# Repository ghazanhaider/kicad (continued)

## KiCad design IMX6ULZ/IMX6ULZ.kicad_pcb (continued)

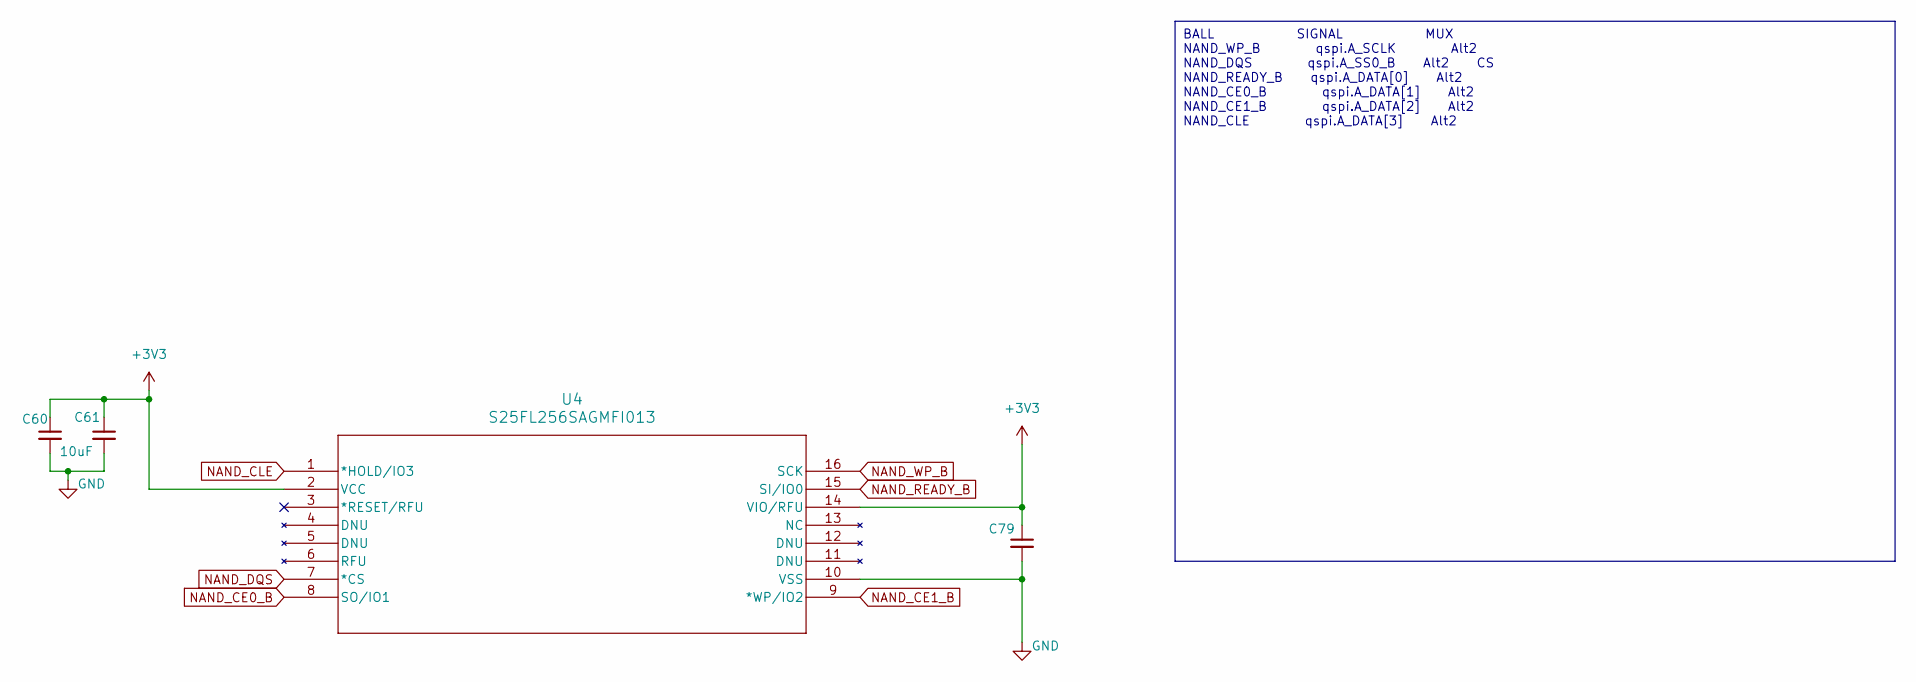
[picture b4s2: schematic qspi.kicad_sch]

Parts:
C60, C79: 0.22uF; C_0402_1005Metric
C61: 10uF; C_0402_1005Metric
U4: S25FL256SAGMFI013; SO3016_SPA

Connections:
3V3: C60.1, C61.1, C79.1, U4.2 (VCC), U4.14 (VIO/RFU); also elsewhere on the board
GND: C60.2, C61.2, C79.2, U4.10 (VSS); also elsewhere on the board
NAND_CE0_B: U4.8 (SO/IO1); also elsewhere on the board
NAND_CE1_B: U4.9 (*WP/IO2); also elsewhere on the board
NAND_CLE: U4.1 (*HOLD/IO3); also elsewhere on the board
NAND_DQS: U4.7 (*CS); also elsewhere on the board
NAND_READY_B: U4.15 (SI/IO0); also elsewhere on the board
NAND_WP_B: U4.16 (SCK); also elsewhere on the board

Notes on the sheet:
BALL SIGNAL MUX NAND_WP_B qspi.A_SCLK Alt2 NAND_DQS qspi.A_SS0_B Alt2 CS NAND_READY_B qspi.A_DATA[0] Alt2 NAND_CE0_B qspi.A_DATA[1] Alt2 NAND_CE1_B qspi.A_DATA[2] Alt2 NAND_CLE qspi.A_DATA[3] Alt2

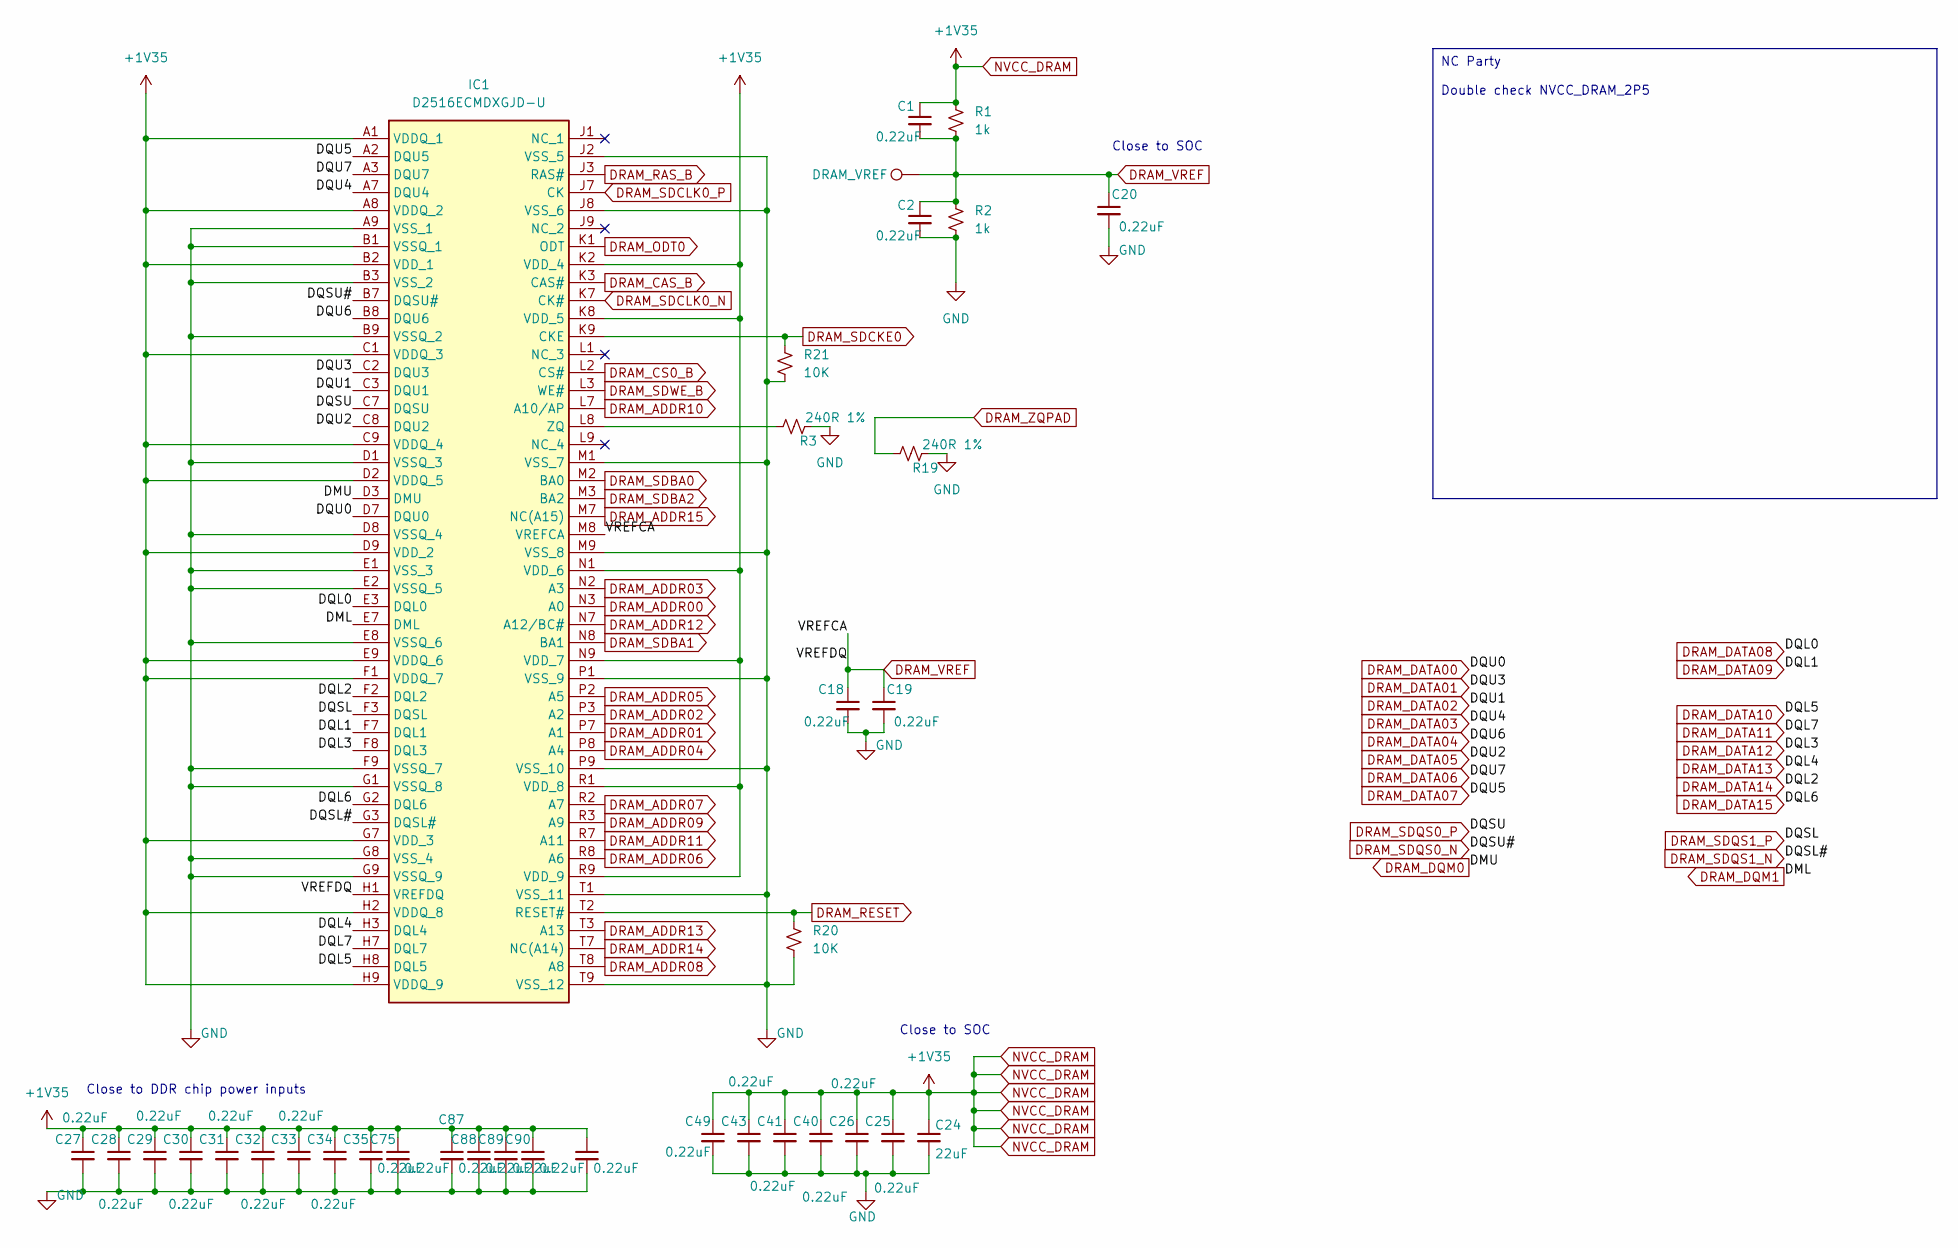
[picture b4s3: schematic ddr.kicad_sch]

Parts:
C1, C2, C18, C19: 0.22uF; C_0402_1005Metric
C20, C25, C26, C27, C28, C29, C30, C31, C32, C33, C34, C35, C40, C41, C43, C49, C75, C87, C88, C89, C90, C92: 0.22uF; C_0201_0603Metric
C24: 22uF; C_0402_1005Metric
IC1: D2516ECMDXGJD-U; Micron_FBGA-96_7.5x13.5mm_Layout9x16_P0.8mm; Mouser Part Number D1216ECMDXGJD-U
R1, R2: 1k; R_0402_1005Metric
R3, R19: 240R 1%; R_0402_1005Metric
R20, R21: 10K; R_0402_1005Metric
TP5: DRAM_VREF; TestPoint_Pad_D1.0mm

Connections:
1V35: C1.1, C24.1, C25.1, C26.1, C27.1, C28.1, C29.1, C30.1, C31.1, C32.1, C33.1, C34.1, C35.1, C40.1, C41.1, C43.1, C49.1, C75.1, C87.1, C88.1, C89.1, C90.1, C92.1, IC1.A1 (VDDQ_1), IC1.A8 (VDDQ_2), IC1.B2 (VDD_1), IC1.C1 (VDDQ_3), IC1.C9 (VDDQ_4), IC1.D2 (VDDQ_5), IC1.D9 (VDD_2), IC1.E9 (VDDQ_6), IC1.F1 (VDDQ_7), IC1.G7 (VDD_3), IC1.H2 (VDDQ_8), IC1.H9 (VDDQ_9), IC1.K2 (VDD_4), IC1.K8 (VDD_5), IC1.N1 (VDD_6), IC1.N9 (VDD_7), IC1.R1 (VDD_8), IC1.R9 (VDD_9), R1.1; also elsewhere on the board
DRAM_ADDR00: IC1.N3 (A0); also elsewhere on the board
DRAM_ADDR01: IC1.P7 (A1); also elsewhere on the board
DRAM_ADDR02: IC1.P3 (A2); also elsewhere on the board
DRAM_ADDR03: IC1.N2 (A3); also elsewhere on the board
DRAM_ADDR04: IC1.P8 (A4); also elsewhere on the board
DRAM_ADDR05: IC1.P2 (A5); also elsewhere on the board
DRAM_ADDR06: IC1.R8 (A6); also elsewhere on the board
DRAM_ADDR07: IC1.R2 (A7); also elsewhere on the board
DRAM_ADDR08: IC1.T8 (A8); also elsewhere on the board
DRAM_ADDR09: IC1.R3 (A9); also elsewhere on the board
DRAM_ADDR10: IC1.L7 (A10/AP); also elsewhere on the board
DRAM_ADDR11: IC1.R7 (A11); also elsewhere on the board
DRAM_ADDR12: IC1.N7 (A12/BC#); also elsewhere on the board
DRAM_ADDR13: IC1.T3 (A13); also elsewhere on the board
DRAM_ADDR14: IC1.T7 (NC(A14)); also elsewhere on the board
DRAM_ADDR15: IC1.M7 (NC(A15)); also elsewhere on the board
DRAM_CAS_B: IC1.K3 (CAS#); also elsewhere on the board
DRAM_CS0_B: IC1.L2 (CS#); also elsewhere on the board
DRAM_DATA00: IC1.D7 (DQU0); also elsewhere on the board
DRAM_DATA01: IC1.C2 (DQU3); also elsewhere on the board
DRAM_DATA02: IC1.C3 (DQU1); also elsewhere on the board
DRAM_DATA03: IC1.A7 (DQU4); also elsewhere on the board
DRAM_DATA04: IC1.B8 (DQU6); also elsewhere on the board
DRAM_DATA05: IC1.C8 (DQU2); also elsewhere on the board
DRAM_DATA06: IC1.A3 (DQU7); also elsewhere on the board
DRAM_DATA07: IC1.A2 (DQU5); also elsewhere on the board
DRAM_DATA08: IC1.E3 (DQL0); also elsewhere on the board
DRAM_DATA09: IC1.F7 (DQL1); also elsewhere on the board
DRAM_DATA10: IC1.H8 (DQL5); also elsewhere on the board
DRAM_DATA11: IC1.H7 (DQL7); also elsewhere on the board
DRAM_DATA12: IC1.F8 (DQL3); also elsewhere on the board
DRAM_DATA13: IC1.H3 (DQL4); also elsewhere on the board
DRAM_DATA14: IC1.F2 (DQL2); also elsewhere on the board
DRAM_DATA15: IC1.G2 (DQL6); also elsewhere on the board
DRAM_DQM0: IC1.D3 (DMU); also elsewhere on the board
DRAM_DQM1: IC1.E7 (DML); also elsewhere on the board
DRAM_ODT0: IC1.K1 (ODT); also elsewhere on the board
DRAM_RAS_B: IC1.J3 (RAS#); also elsewhere on the board
DRAM_RESET: IC1.T2 (RESET#), R20.1; also elsewhere on the board
DRAM_SDBA0: IC1.M2 (BA0); also elsewhere on the board
DRAM_SDBA1: IC1.N8 (BA1); also elsewhere on the board
DRAM_SDBA2: IC1.M3 (BA2); also elsewhere on the board
DRAM_SDCKE0: IC1.K9 (CKE), R21.1; also elsewhere on the board
DRAM_SDCLK0_N: IC1.K7 (CK#); also elsewhere on the board
DRAM_SDCLK0_P: IC1.J7 (CK); also elsewhere on the board
DRAM_SDQS0_N: IC1.B7 (DQSU#); also elsewhere on the board
DRAM_SDQS0_P: IC1.C7 (DQSU); also elsewhere on the board
DRAM_SDQS1_N: IC1.G3 (DQSL#); also elsewhere on the board
DRAM_SDQS1_P: IC1.F3 (DQSL); also elsewhere on the board
DRAM_SDWE_B: IC1.L3 (WE#); also elsewhere on the board
DRAM_VREF: C1.2, C2.1, C18.1, C19.1, C20.1, IC1.H1 (VREFDQ), IC1.M8 (VREFCA), R1.2, R2.1, TP5.1; also elsewhere on the board
DRAM_ZQPAD: R19.1; also elsewhere on the board
GND: C2.2, C18.2, C19.2, C20.2, C24.2, C25.2, C26.2, C27.2, C28.2, C29.2, C30.2, C31.2, C32.2, C33.2, C34.2, C35.2, C40.2, C41.2, C43.2, C49.2, C75.2, C87.2, C88.2, C89.2, C90.2, C92.2, IC1.A9 (VSS_1), IC1.B1 (VSSQ_1), IC1.B3 (VSS_2), IC1.B9 (VSSQ_2), IC1.D1 (VSSQ_3), IC1.D8 (VSSQ_4), IC1.E1 (VSS_3), IC1.E2 (VSSQ_5), IC1.E8 (VSSQ_6), IC1.F9 (VSSQ_7), IC1.G1 (VSSQ_8), IC1.G8 (VSS_4), IC1.G9 (VSSQ_9), IC1.J2 (VSS_5), IC1.J8 (VSS_6), IC1.M1 (VSS_7), IC1.M9 (VSS_8), IC1.P1 (VSS_9), IC1.P9 (VSS_10), IC1.T1 (VSS_11), IC1.T9 (VSS_12), R2.2, R3.2, R19.2, R20.2, R21.2; also elsewhere on the board
unnamed: IC1.L8 (ZQ), R3.1

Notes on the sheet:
NC Party Double check NVCC_DRAM_2P5
Close to SOC
Close to DDR chip power inputs

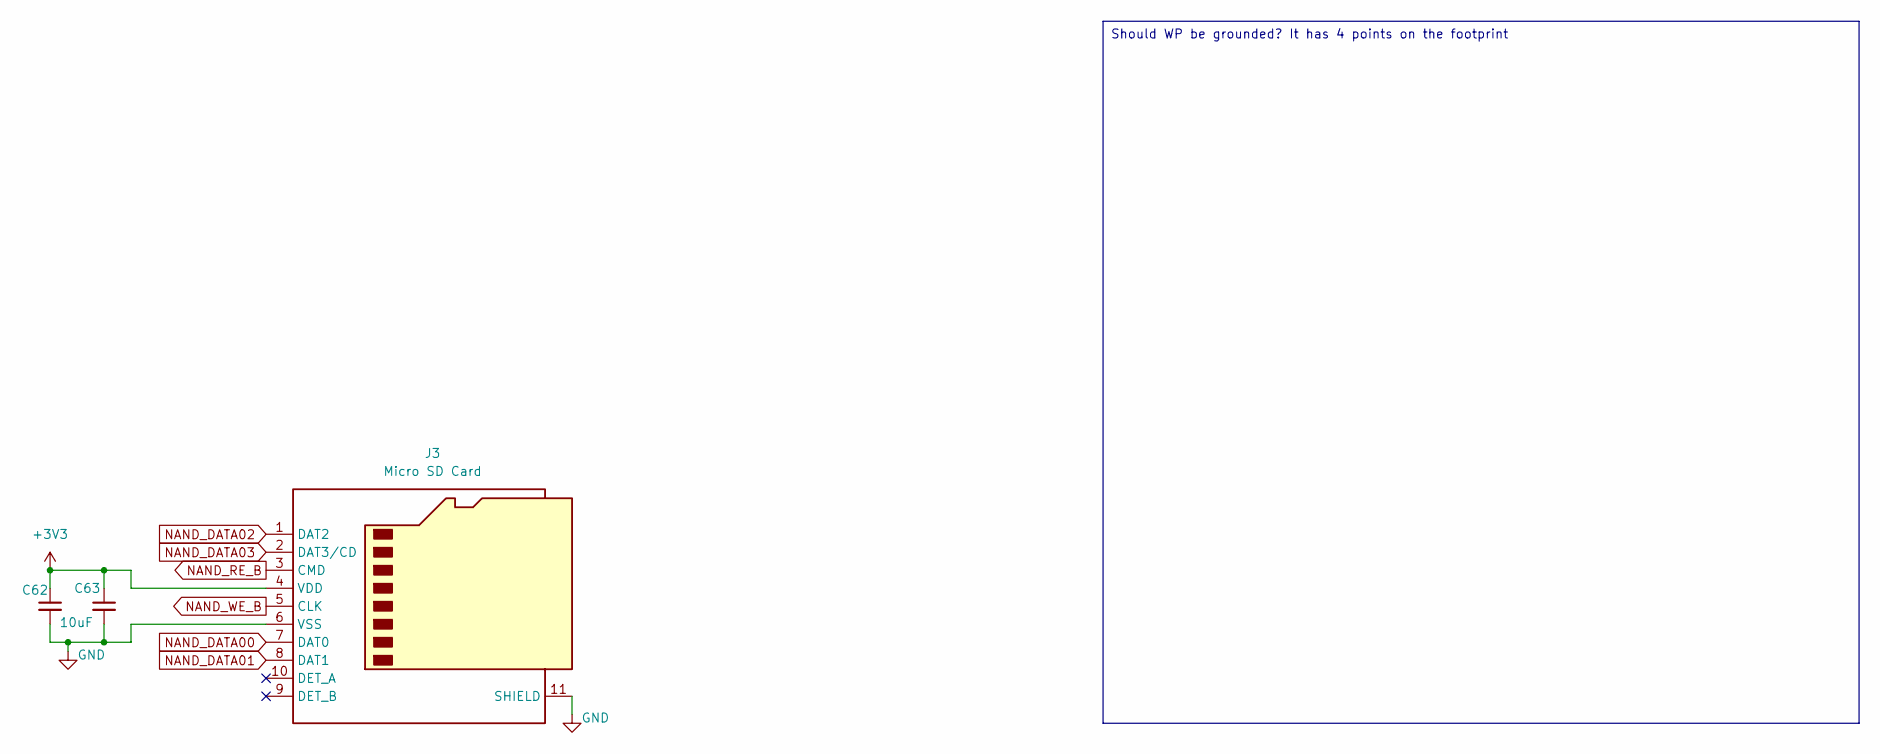
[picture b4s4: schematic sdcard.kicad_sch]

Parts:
C62: 0.22uF; C_0402_1005Metric
C63: 10uF; C_0402_1005Metric
J3: Micro SD Card; microSD_HC_Hirose_DM3D-SF

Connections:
3V3: C62.1, C63.1, J3.4 (VDD); also elsewhere on the board
GND: C62.2, C63.2, J3.6 (VSS), J3.11 (SHIELD); also elsewhere on the board
NAND_DATA00: J3.7 (DAT0); also elsewhere on the board
NAND_DATA01: J3.8 (DAT1); also elsewhere on the board
NAND_DATA02: J3.1 (DAT2); also elsewhere on the board
NAND_DATA03: J3.2 (DAT3/CD); also elsewhere on the board
NAND_RE_B: J3.3 (CMD); also elsewhere on the board
NAND_WE_B: J3.5 (CLK); also elsewhere on the board

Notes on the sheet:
Should WP be grounded? It has 4 points on the footprint

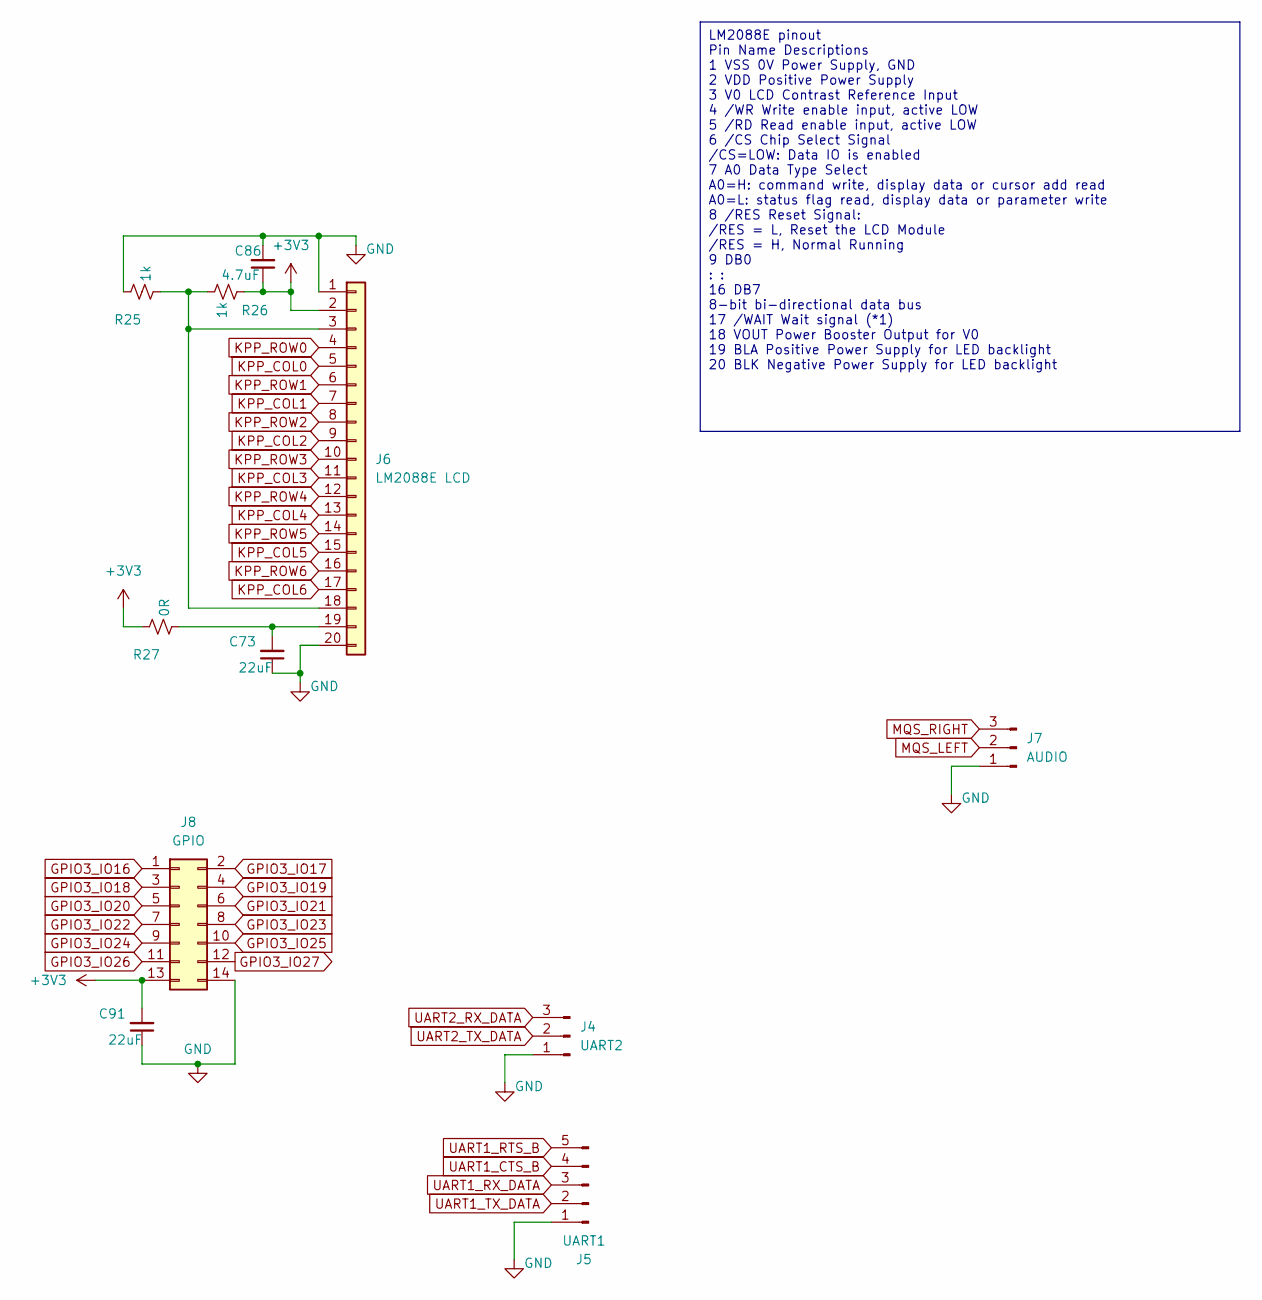
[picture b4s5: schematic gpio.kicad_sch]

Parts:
C73, C91: 22uF; C_0805_2012Metric
C86: 4.7uF; C_0805_2012Metric
J4: UART2; PinHeader_1x03_P2.54mm_Vertical
J5: UART1; PinHeader_1x05_P2.54mm_Vertical
J6: LM2088E LCD; PinHeader_1x20_P2.54mm_Vertical
J7: AUDIO; PinHeader_1x03_P2.54mm_Vertical
J8: GPIO; PinHeader_2x07_P2.54mm_Vertical
R25, R26: 1k; R_0402_1005Metric
R27: 0R; R_0805_2012Metric

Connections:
3V3: C86.1, C91.2, J6.2, J8.13, R26.1, R27.1; also elsewhere on the board
GND: C73.1, C86.2, C91.1, J4.1, J5.1, J6.1, J6.20, J7.1, J8.14, R25.1; also elsewhere on the board
GPIO3_IO16: J8.1; also elsewhere on the board
GPIO3_IO17: J8.2; also elsewhere on the board
GPIO3_IO18: J8.3; also elsewhere on the board
GPIO3_IO19: J8.4; also elsewhere on the board
GPIO3_IO20: J8.5; also elsewhere on the board
GPIO3_IO21: J8.6; also elsewhere on the board
GPIO3_IO22: J8.7; also elsewhere on the board
GPIO3_IO23: J8.8; also elsewhere on the board
GPIO3_IO24: J8.9; also elsewhere on the board
GPIO3_IO25: J8.10; also elsewhere on the board
GPIO3_IO26: J8.11; also elsewhere on the board
GPIO3_IO27: J8.12; also elsewhere on the board
KPP_COL0: J6.5; also elsewhere on the board
KPP_COL1: J6.7; also elsewhere on the board
KPP_COL2: J6.9; also elsewhere on the board
KPP_COL3: J6.11; also elsewhere on the board
KPP_COL4: J6.13; also elsewhere on the board
KPP_COL5: J6.15; also elsewhere on the board
KPP_COL6: J6.17; also elsewhere on the board
KPP_ROW0: J6.4; also elsewhere on the board
KPP_ROW1: J6.6; also elsewhere on the board
KPP_ROW2: J6.8; also elsewhere on the board
KPP_ROW3: J6.10; also elsewhere on the board
KPP_ROW4: J6.12; also elsewhere on the board
KPP_ROW5: J6.14; also elsewhere on the board
KPP_ROW6: J6.16; also elsewhere on the board
MQS_LEFT: J7.2; also elsewhere on the board
MQS_RIGHT: J7.3; also elsewhere on the board
unnamed: J6.3, J6.18, R25.2, R26.2
unnamed: C73.2, J6.19, R27.2
UART1_CTS_B: J5.4; also elsewhere on the board
UART1_RTS_B: J5.5; also elsewhere on the board
UART1_RX_DATA: J5.3; also elsewhere on the board
UART1_TX_DATA: J5.2; also elsewhere on the board
UART2_RX_DATA: J4.3; also elsewhere on the board
UART2_TX_DATA: J4.2; also elsewhere on the board

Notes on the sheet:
LM2088E pinout Pin Name Descriptions 1 VSS 0V Power Supply, GND 2 VDD Positive Power Supply 3 V0 LCD Contrast Reference Input 4 /WR Write enable input, active LOW 5 /RD Read enable input, active LOW 6 /CS Chip Select Signal /CS=LOW: Data IO is enabled 7 A0 Data Type Select A0=H: command write, disp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

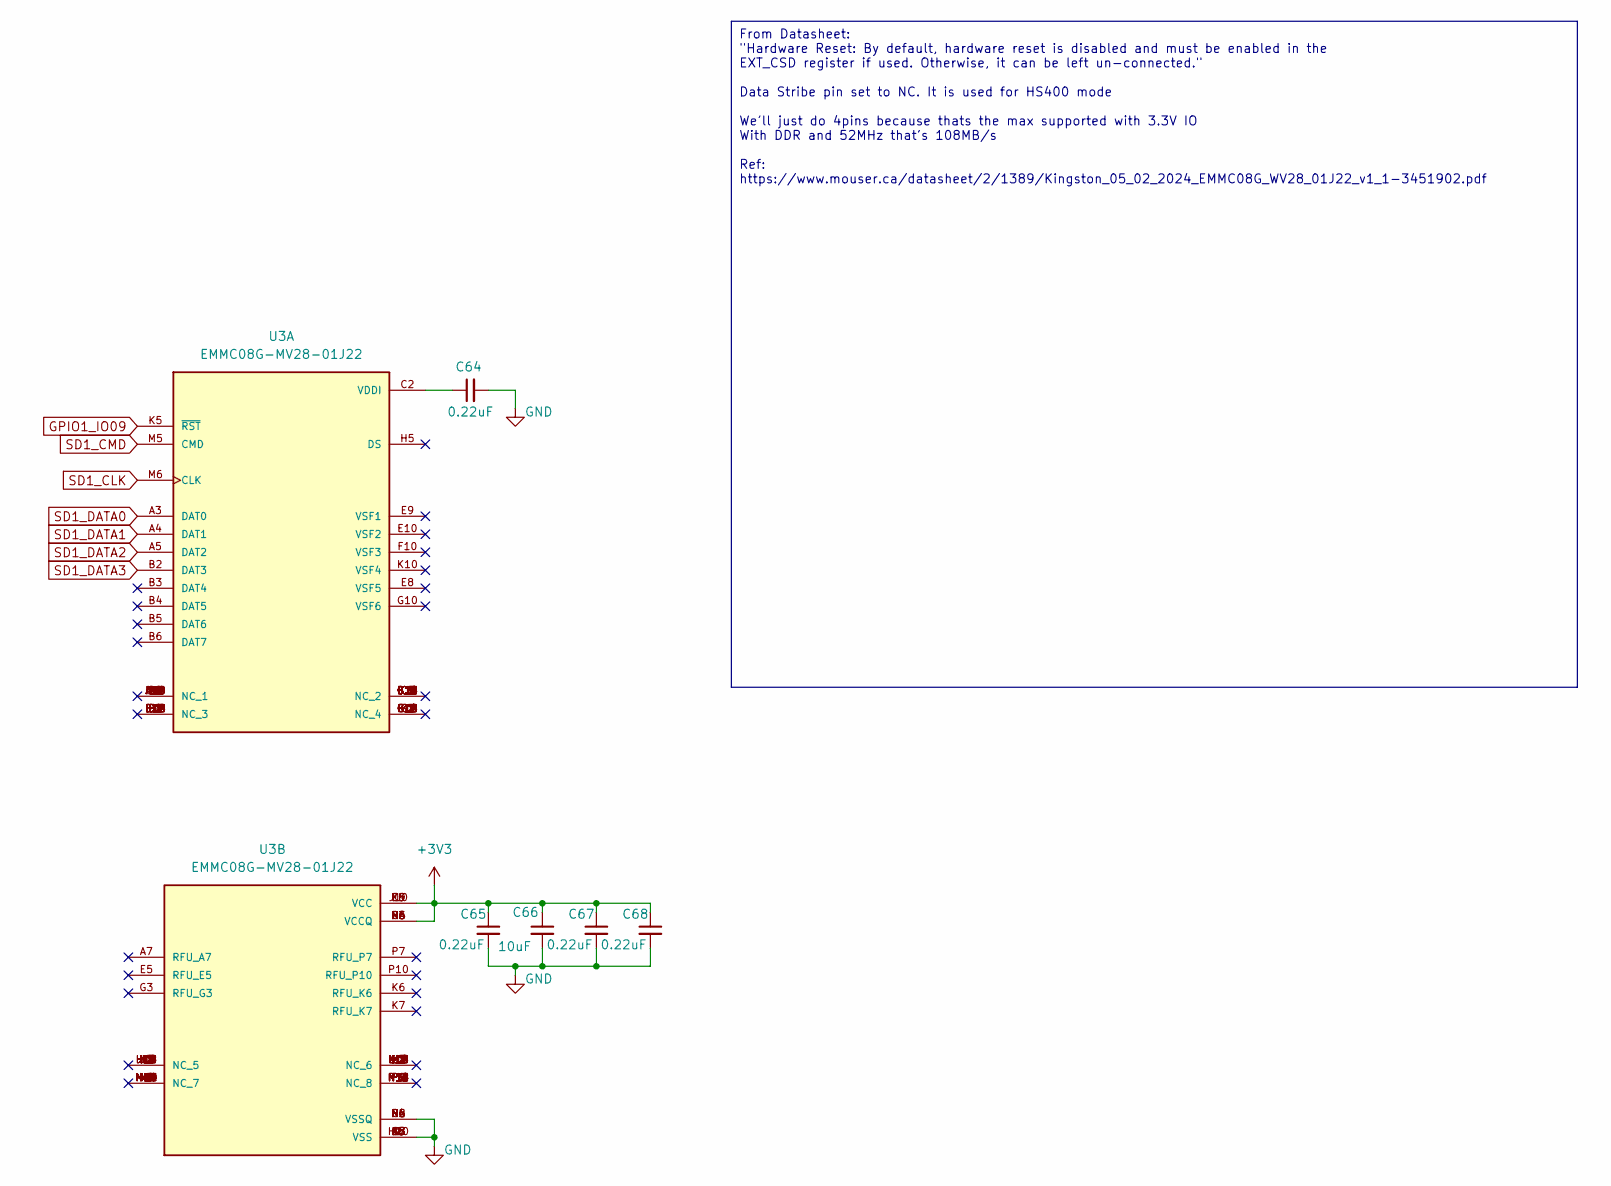
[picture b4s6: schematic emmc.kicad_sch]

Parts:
C64, C65, C67, C68: 0.22uF; C_0402_1005Metric
C66: 10uF; C_0402_1005Metric
U3: EMMC08G-MV28-01J22; BGA153N50P14X14_1300X1150X100N; PARTREV N/A

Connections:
3V3: C65.1, C66.1, C67.1, C68.1, U3.C6 (VCCQ), U3.E6 (VCC), U3.F5 (VCC), U3.J10 (VCC), U3.K9 (VCC), U3.M4 (VCCQ), U3.N4 (VCCQ), U3.P3 (VCCQ), U3.P5 (VCCQ); also elsewhere on the board
GND: C64.2, C65.2, C66.2, C67.2, C68.2, U3.A6 (VSS), U3.C4 (VSSQ), U3.E7 (VSS), U3.G5 (VSS), U3.H10 (VSS), U3.J5 (VSS), U3.K8 (VSS), U3.N2 (VSSQ), U3.N5 (VSSQ), U3.P4 (VSSQ), U3.P6 (VSSQ); also elsewhere on the board
GPIO1_IO09: U3.K5 (~RST); also elsewhere on the board
unnamed: C64.1, U3.C2 (VDDI)
SD1_CLK: U3.M6 (CLK); also elsewhere on the board
SD1_CMD: U3.M5 (CMD); also elsewhere on the board
SD1_DATA0: U3.A3 (DAT0); also elsewhere on the board
SD1_DATA1: U3.A4 (DAT1); also elsewhere on the board
SD1_DATA2: U3.A5 (DAT2); also elsewhere on the board
SD1_DATA3: U3.B2 (DAT3); also elsewhere on the board

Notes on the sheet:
From Datasheet: "Hardware Reset: By default, hardware reset is disabled and must be enabled in the EXT_CSD register if used. Otherwise, it can be left un-connected." Data Stribe pin set to NC. It is used for HS400 mode We'll just do 4pins because thats the max supported with 3.3V IO With DDR and 52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

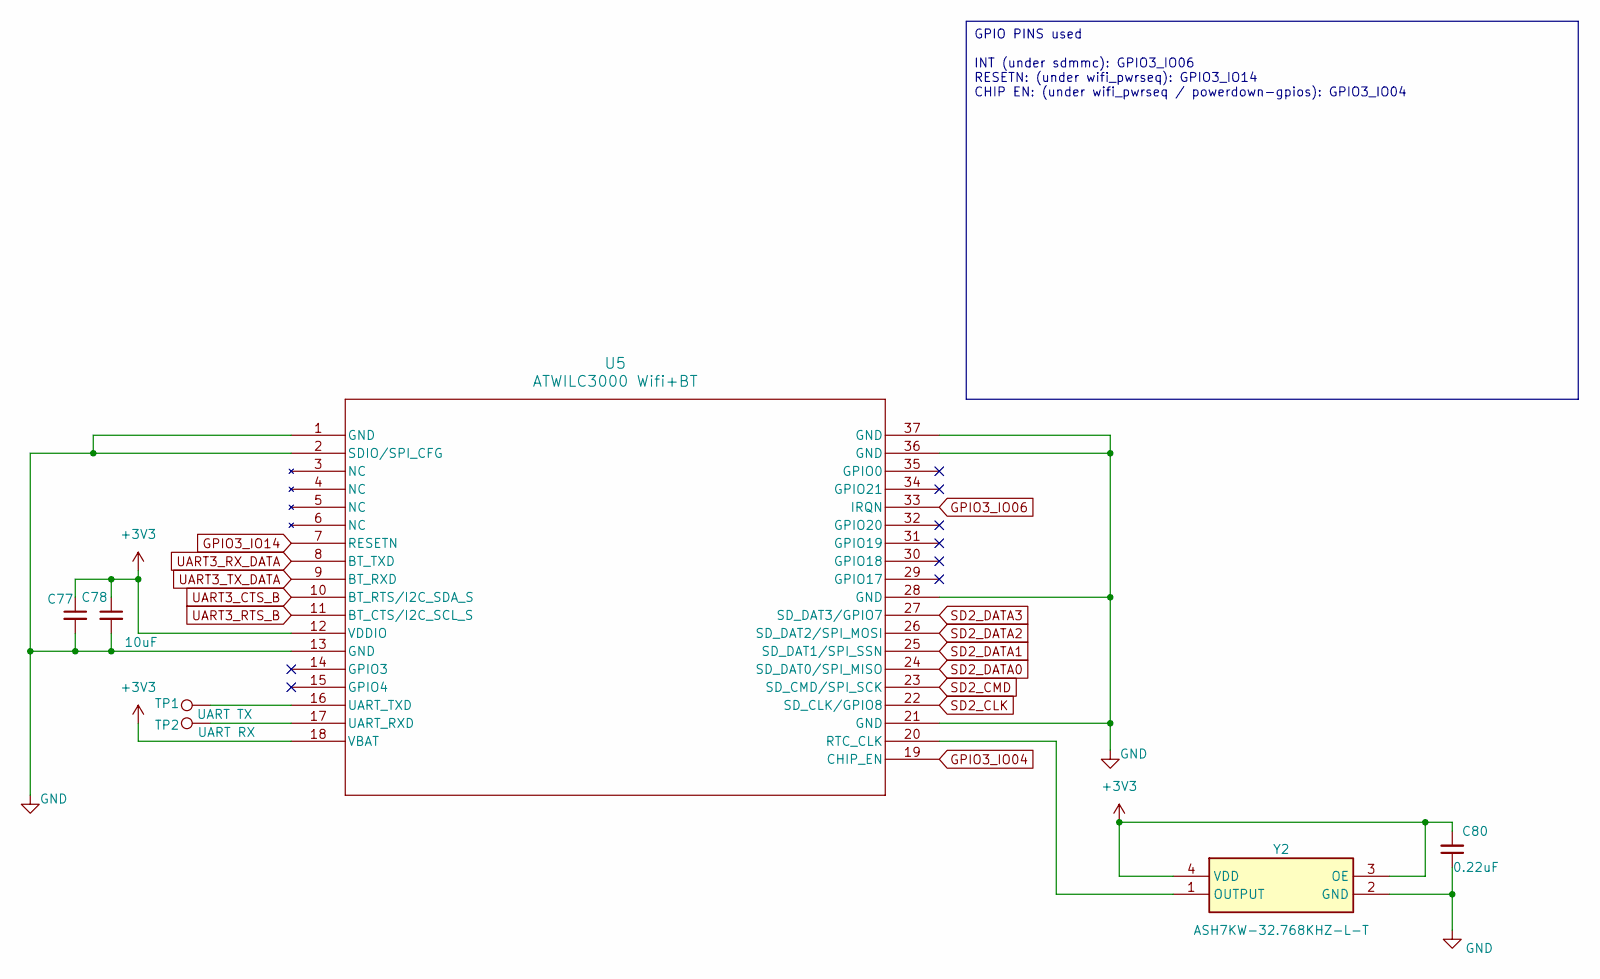
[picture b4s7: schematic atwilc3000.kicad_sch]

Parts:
C77, C80: 0.22uF; C_0402_1005Metric
C78: 10uF; C_0402_1005Metric
TP1: UART TX; TestPoint_Pad_D1.0mm
TP2: UART RX; TestPoint_Pad_D1.0mm
U5: ATWILC3000 Wifi+BT; ATWILC3000-MR110CA_MCH
Y2: ASH7KW-32.768KHZ-L-T; ASH7KW32768kHzLT; Mouser Part Number 815-ASH7KW-32.7-L-T

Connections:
3V3: C77.1, C78.1, C80.2, U5.12 (VDDIO), U5.18 (VBAT), Y2.3 (OE), Y2.4 (VDD); also elsewhere on the board
GND: C77.2, C78.2, C80.1, U5.1 (GND), U5.2 (SDIO/SPI_CFG), U5.13 (GND), U5.21 (GND), U5.28 (GND), U5.36 (GND), U5.37 (GND), Y2.2 (GND); also elsewhere on the board
GPIO3_IO04: U5.19 (CHIP_EN); also elsewhere on the board
GPIO3_IO06: U5.33 (IRQN); also elsewhere on the board
GPIO3_IO14: U5.7 (RESETN); also elsewhere on the board
unnamed: U5.20 (RTC_CLK), Y2.1 (OUTPUT)
unnamed: TP2.1, U5.17 (UART_RXD)
unnamed: TP1.1, U5.16 (UART_TXD)
SD2_CLK: U5.22 (SD_CLK/GPIO8); also elsewhere on the board
SD2_CMD: U5.23 (SD_CMD/SPI_SCK); also elsewhere on the board
SD2_DATA0: U5.24 (SD_DAT0/SPI_MISO); also elsewhere on the board
SD2_DATA1: U5.25 (SD_DAT1/SPI_SSN); also elsewhere on the board
SD2_DATA2: U5.26 (SD_DAT2/SPI_MOSI); also elsewhere on the board
SD2_DATA3: U5.27 (SD_DAT3/GPIO7); also elsewhere on the board
UART3_CTS_B: U5.10 (BT_RTS/I2C_SDA_S); also elsewhere on the board
UART3_RTS_B: U5.11 (BT_CTS/I2C_SCL_S); also elsewhere on the board
UART3_RX_DATA: U5.8 (BT_TXD); also elsewhere on the board
UART3_TX_DATA: U5.9 (BT_RXD); also elsewhere on the board

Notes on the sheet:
GPIO PINS used INT (under sdmmc): GPIO3_IO06 RESETN: (under wifi_pwrseq): GPIO3_IO14 CHIP EN: (under wifi_pwrseq / powerdown-gpios): GPIO3_IO04

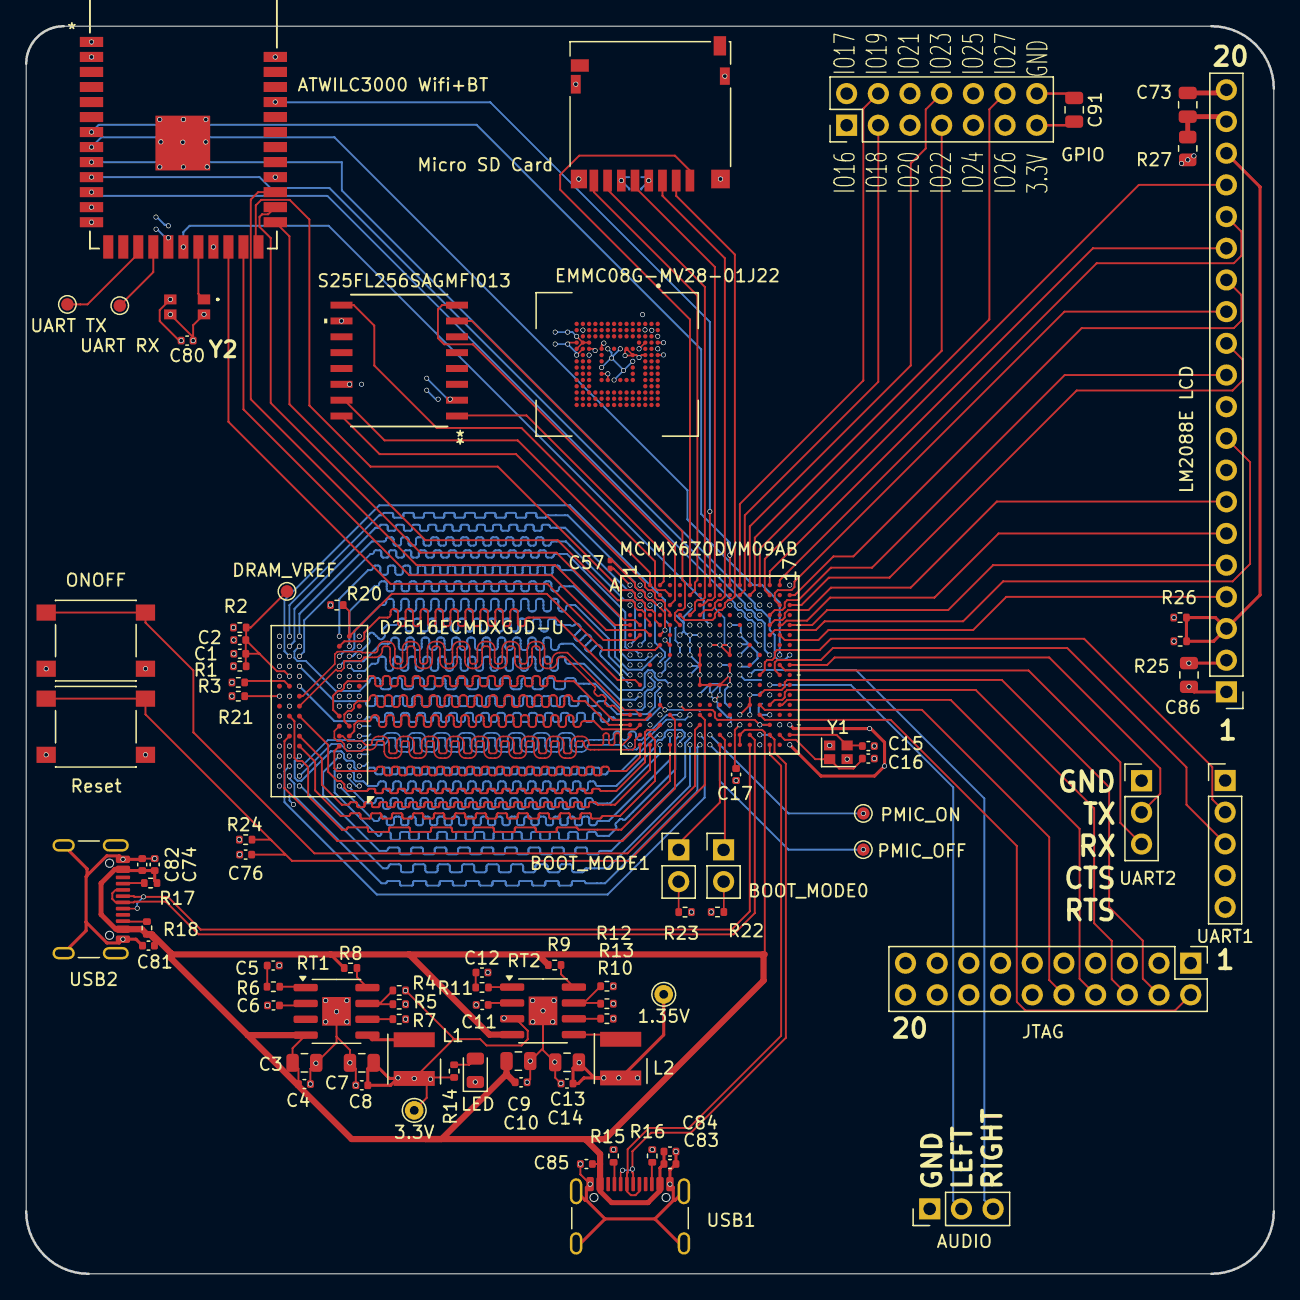
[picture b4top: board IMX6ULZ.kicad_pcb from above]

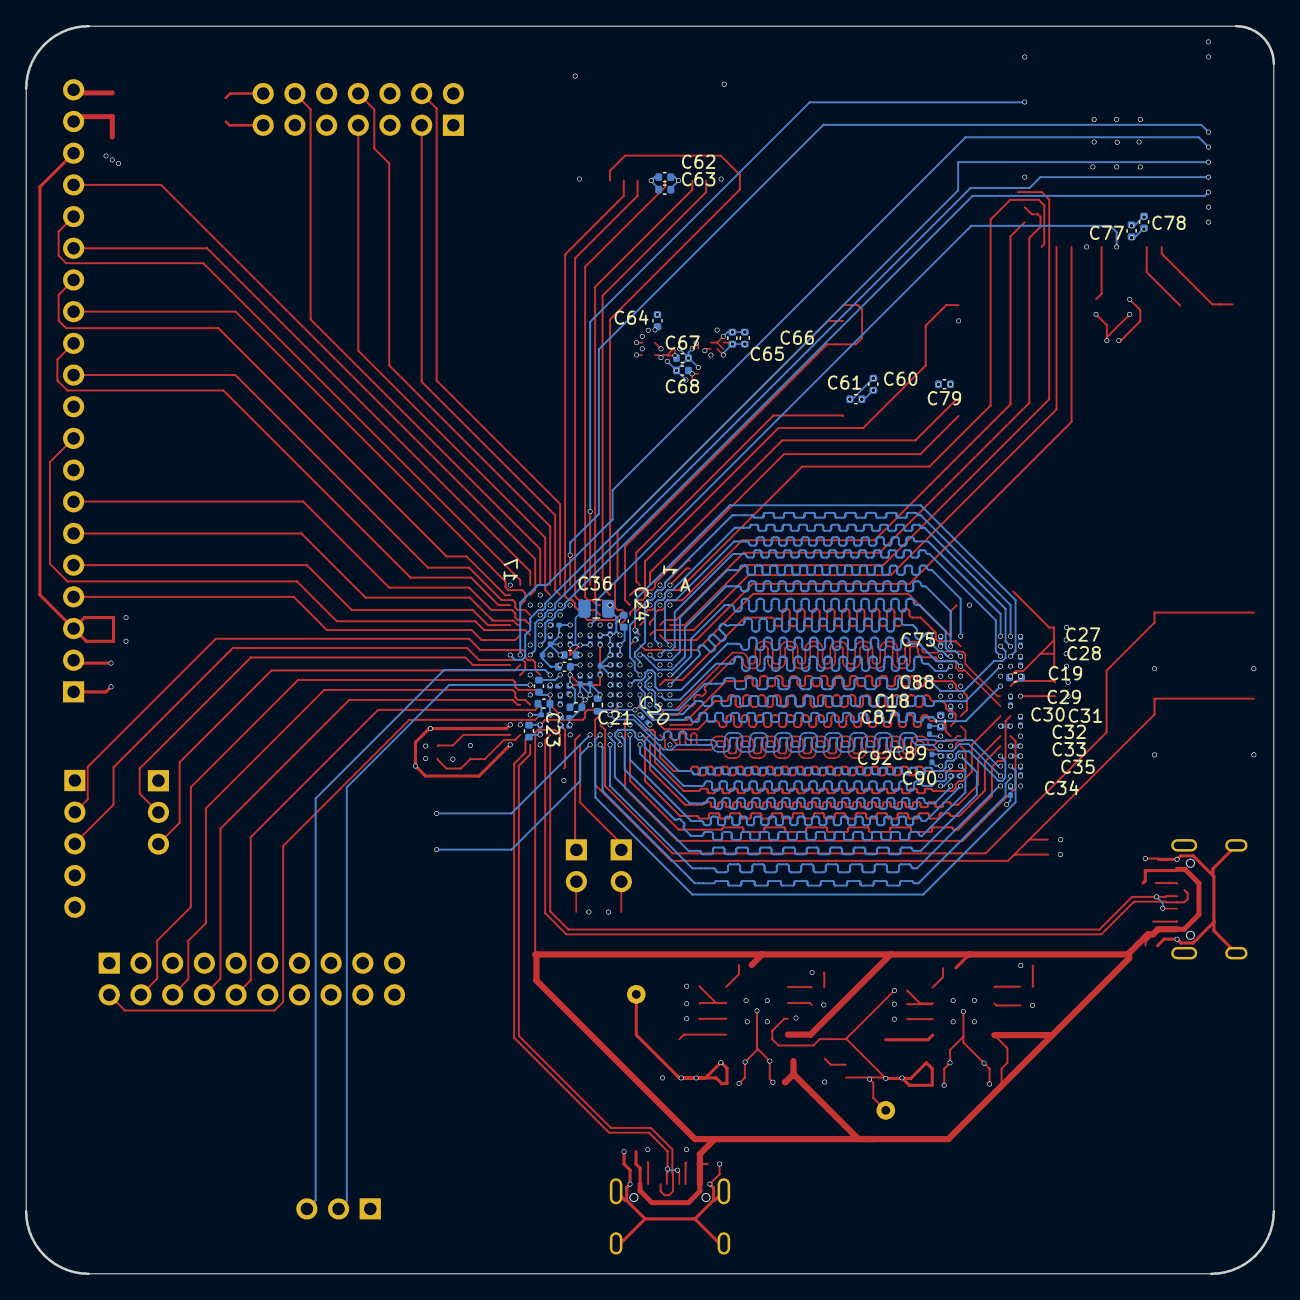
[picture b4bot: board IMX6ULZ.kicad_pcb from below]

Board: 6 copper layers, 100.0 x 100.0 mm, 151 parts (64 on the bottom side), 173 nets.

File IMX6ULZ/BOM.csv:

"Reference","Value","Footprint","Qty","DNP"
"SW1","ONOFF","Button_Switch_SMD:SW_SPST_PTS645","1",""
"SW2","Reset","Button_Switch_SMD:SW_SPST_PTS645","1",""
"C22,C25,C26,C27,C28,C29,C30,C31,C32,C33,C34,C35,C37,C38,C39,C40,C41,C42,C43,C45,C46,C47,C49,C50,C51,C52,C53,C54,C55,C57,C58,C69,C71,C72,C75,C87,C88,C89,C90,C92","0.22uF","Capacitor_SMD:C_0201_0603Metric","40",""
"C20","0.22uF","Capacitor_SMD:C_0201_0603Metric_Pad0.64x0.40mm_HandSolder","1",""
"C1,C2,C6,C11,C18,C19,C60,C62,C65,C76,C77,C79,C80,C82,C85","0.22uF","Capacitor_SMD:C_0402_1005Metric","15",""
"C4,C8,C10,C14,C21,C64,C67,C68","0.1uF","Capacitor_SMD:C_0402_1005Metric","8",""
"C5,C12","560pF","Capacitor_SMD:C_0402_1005Metric","2",""
"C15,C16","10pF","Capacitor_SMD:C_0402_1005Metric","2",""
"C17,C23,C48,C61,C63,C66,C78","10uF","Capacitor_SMD:C_0402_1005Metric","7",""
"C24,C44,C59,C81,C84","22uF","Capacitor_SMD:C_0402_1005Metric","5",""
"C56,C70,C74,C83","4.7uF","Capacitor_SMD:C_0402_1005Metric","4",""
"C3,C7,C9,C13,C36,C73","22uF","Capacitor_SMD:C_0805_2012Metric","6",""
"C86","4.7uF","Capacitor_SMD:C_0805_2012Metric","1",""
"J3","Micro SD Card","Connector_Card:microSD_HC_Hirose_DM3D-SF","1",""
"J1","BOOT_MODE0","Connector_PinHeader_2.54mm:PinHeader_1x02_P2.54mm_Vertical","1",""
"J2","BOOT_MODE1","Connector_PinHeader_2.54mm:PinHeader_1x02_P2.54mm_Vertical","1",""
"J4","UART2","Connector_PinHeader_2.54mm:PinHeader_1x03_P2.54mm_Vertical","1",""
"J7","AUDIO","Connector_PinHeader_2.54mm:PinHeader_1x03_P2.54mm_Vertical","1",""
"J5","UART1","Connector_PinHeader_2.54mm:PinHeader_1x05_P2.54mm_Vertical","1",""
"J6","LM2088E LCD","Connector_PinHeader_2.54mm:PinHeader_1x20_P2.54mm_Vertical","1",""
"U2","JTAG","Connector_PinHeader_2.54mm:PinHeader_2x10_P2.54mm_Vertical","1",""
"P1","USB1","Connector_USB:USB_C_Receptacle_GCT_USB4105-xx-A_16P_TopMnt_Horizontal","1",""
"P2","USB2","Connector_USB:USB_C_Receptacle_GCT_USB4105-xx-A_16P_TopMnt_Horizontal","1",""
"Y1","XRCGB24M000FBP12R0","Crystal:Crystal_SMD_2016-4Pin_2.0x1.6mm","1",""
"Y2","ASH7KW-32.768KHZ-L-T","GhazanCustom:ASH7KW32768kHzLT","1",""
"U5","ATWILC3000 Wifi+BT","GhazanCustom:ATWILC3000-MR110CA_MCH","1",""
"U3","EMMC08G-MV28-01J22","GhazanCustom:BGA153N50P14X14_1300X1150X100N","1",""
"U1","MCIMX6Z0DVM09AB","GhazanCustom:MAPBGA289_NXP","1",""
"U4","S25FL256SAGMFI013","GhazanCustom:SO3016_SPA","1",""
"L1,L2","2uH","Inductor_SMD_Wurth:L_Wurth_WE-LQSH-4020","2",""
"D1","LED","LED_SMD:LED_0805_2012Metric","1",""
"IC1","D2516ECMDXGJD-U","Package_BGA:Micron_FBGA-96_7.5x13.5mm_Layout9x16_P0.8mm","1",""
"RT1,RT2","RT8070","Package_SO:HSOP-8-1EP_3.9x4.9mm_P1.27mm_EP2.3x2.3mm","2",""
"R1,R2,R14","1k","Resistor_SMD:R_0402_1005Metric","3",""
"R3,R19","240R 1%","Resistor_SMD:R_0402_1005Metric","2",""
"R4","75k","Resistor_SMD:R_0402_1005Metric","1",""
"R5,R13","24k","Resistor_SMD:R_0402_1005Metric","2",""
"R6","33k","Resistor_SMD:R_0402_1005Metric","1",""
"R7,R8,R9,R10","330k","Resistor_SMD:R_0402_1005Metric","4",""
"R11","12k","Resistor_SMD:R_0402_1005Metric","1",""
"R12","16K5","Resistor_SMD:R_0402_1005Metric","1",""
"R15,R16","5.1k 1%","Resistor_SMD:R_0402_1005Metric","2",""
"R17,R18","56k 1%","Resistor_SMD:R_0402_1005Metric","2",""
"R20,R21,R22,R23,R24","10K","Resistor_SMD:R_0402_1005Metric","5",""
"R25,R26","1k","Resistor_SMD:R_0805_2012Metric","2",""
"R27","0R","Resistor_SMD:R_0805_2012Metric","1",""
"TP1","UART TX","TestPoint:TestPoint_Pad_D1.0mm","1",""
"TP2","UART RX","TestPoint:TestPoint_Pad_D1.0mm","1",""
"TP3","PMIC_ON","TestPoint:TestPoint_Pad_D1.0mm","1",""
"TP4","PMIC_OFF","TestPoint:TestPoint_Pad_D1.0mm","1",""
"TP5","DRAM_VREF","TestPoint:TestPoint_Pad_D1.0mm","1",""
"TP6","3.3V","TestPoint:TestPoint_THTPad_D1.5mm_Drill0.7mm","1",""
"TP7","1.35V","TestPoint:TestPoint_THTPad_D1.5mm_Drill0.7mm","1",""
